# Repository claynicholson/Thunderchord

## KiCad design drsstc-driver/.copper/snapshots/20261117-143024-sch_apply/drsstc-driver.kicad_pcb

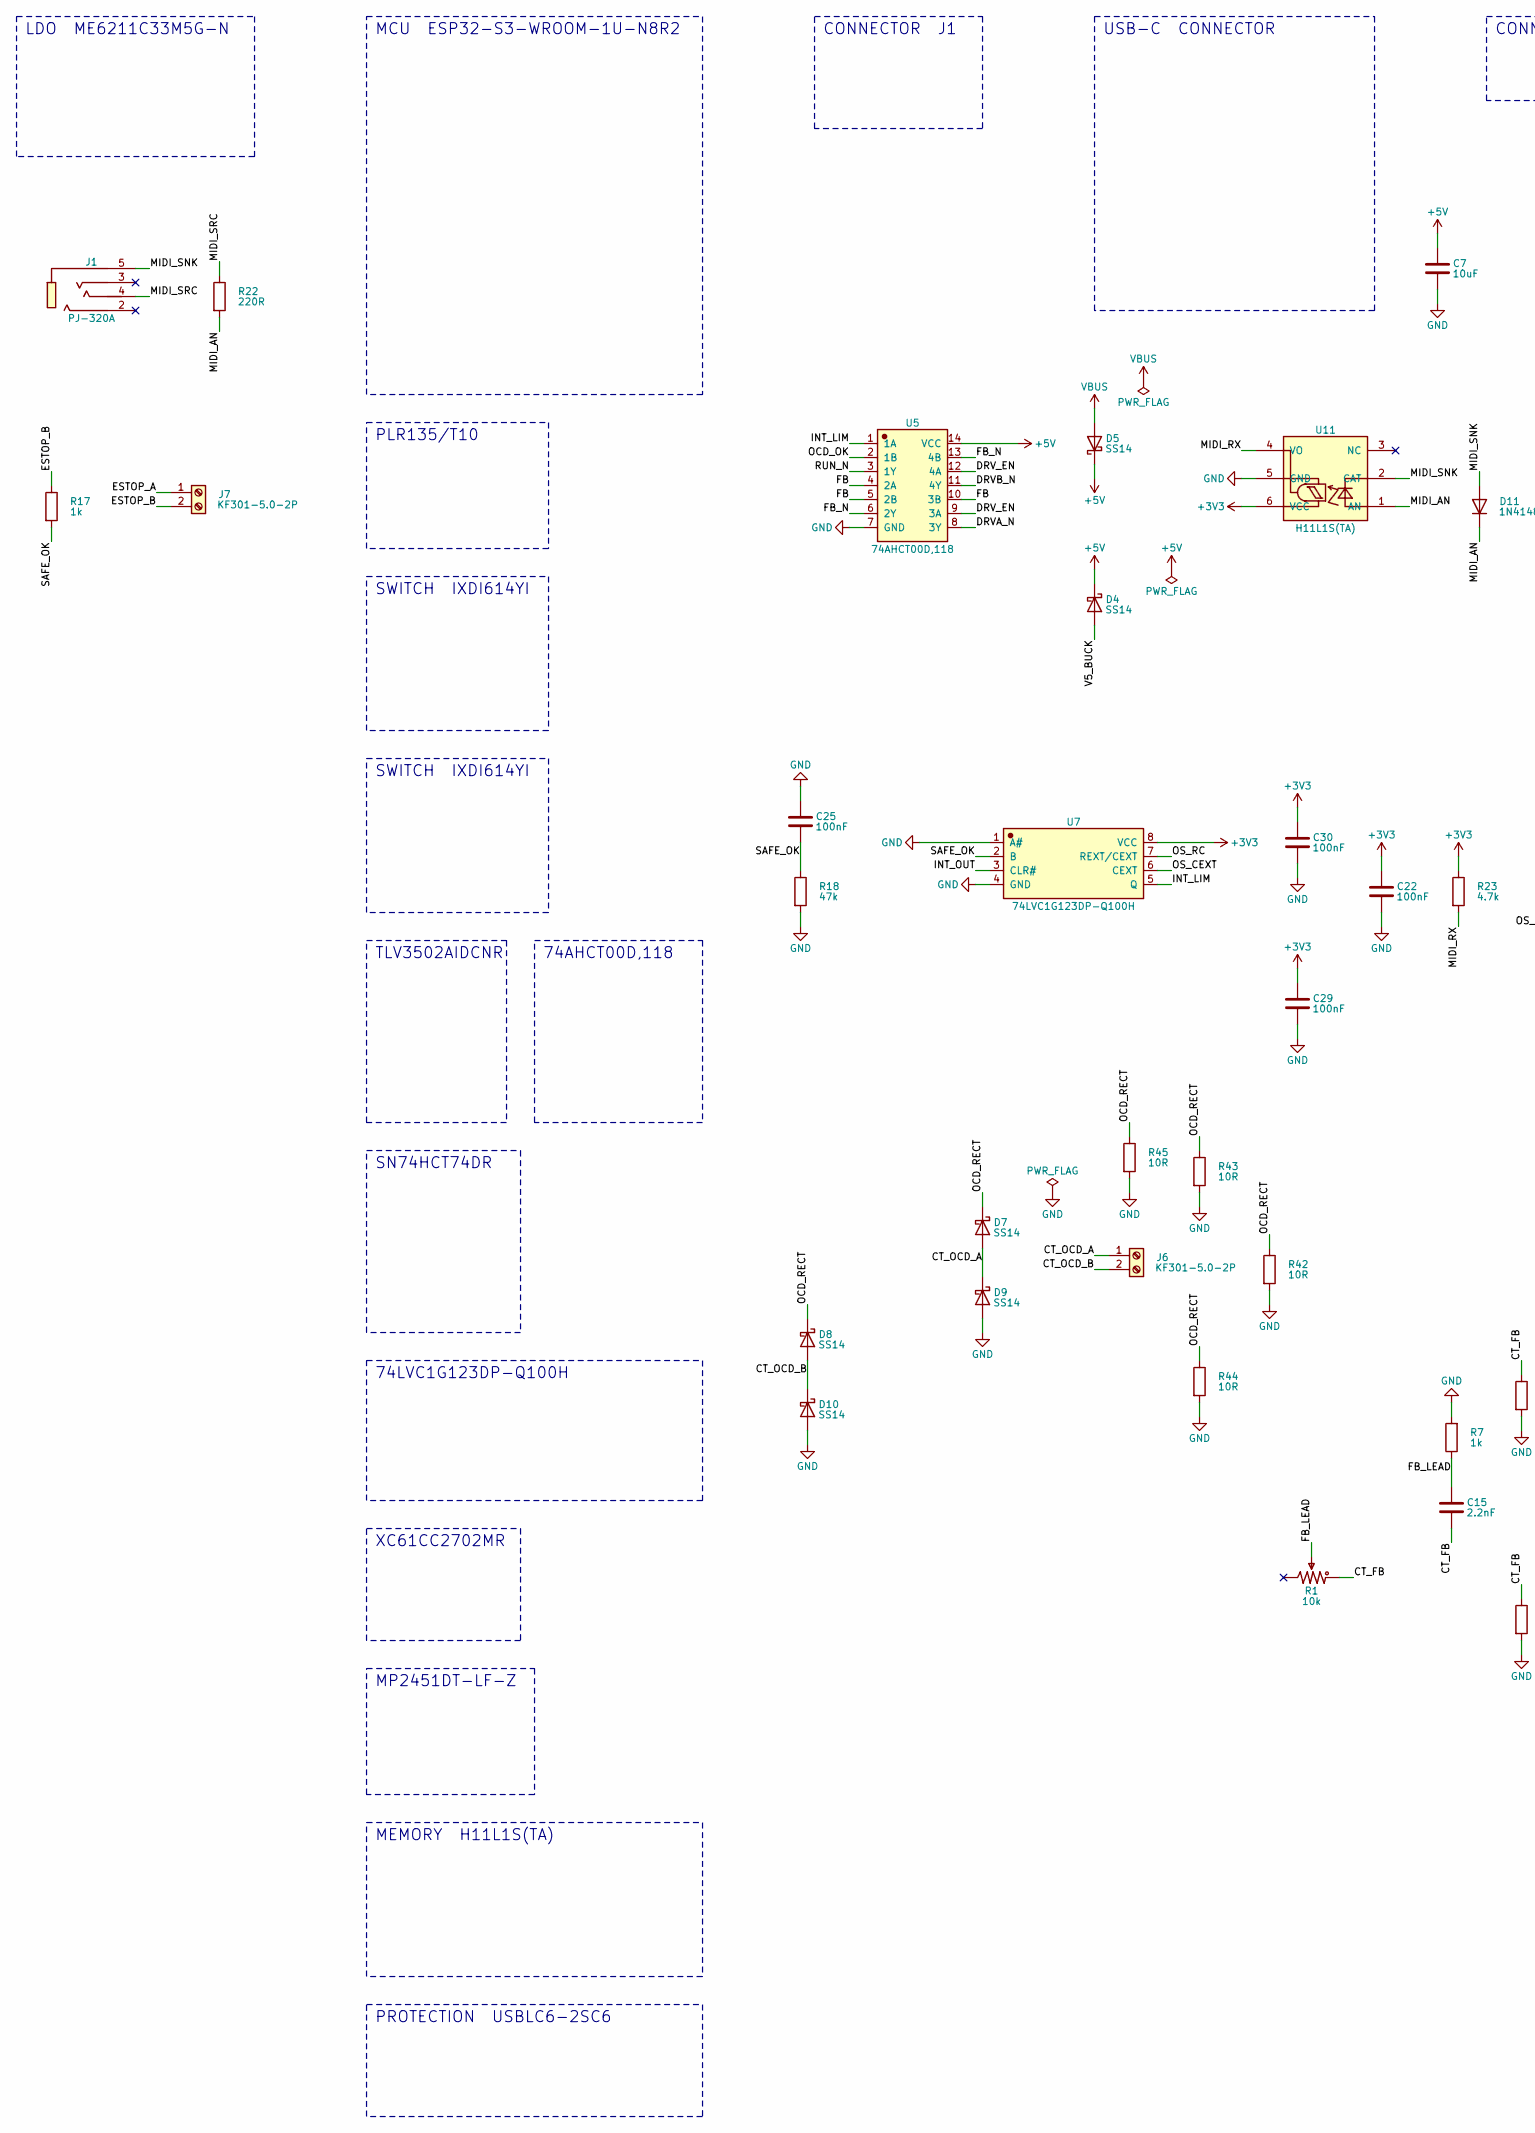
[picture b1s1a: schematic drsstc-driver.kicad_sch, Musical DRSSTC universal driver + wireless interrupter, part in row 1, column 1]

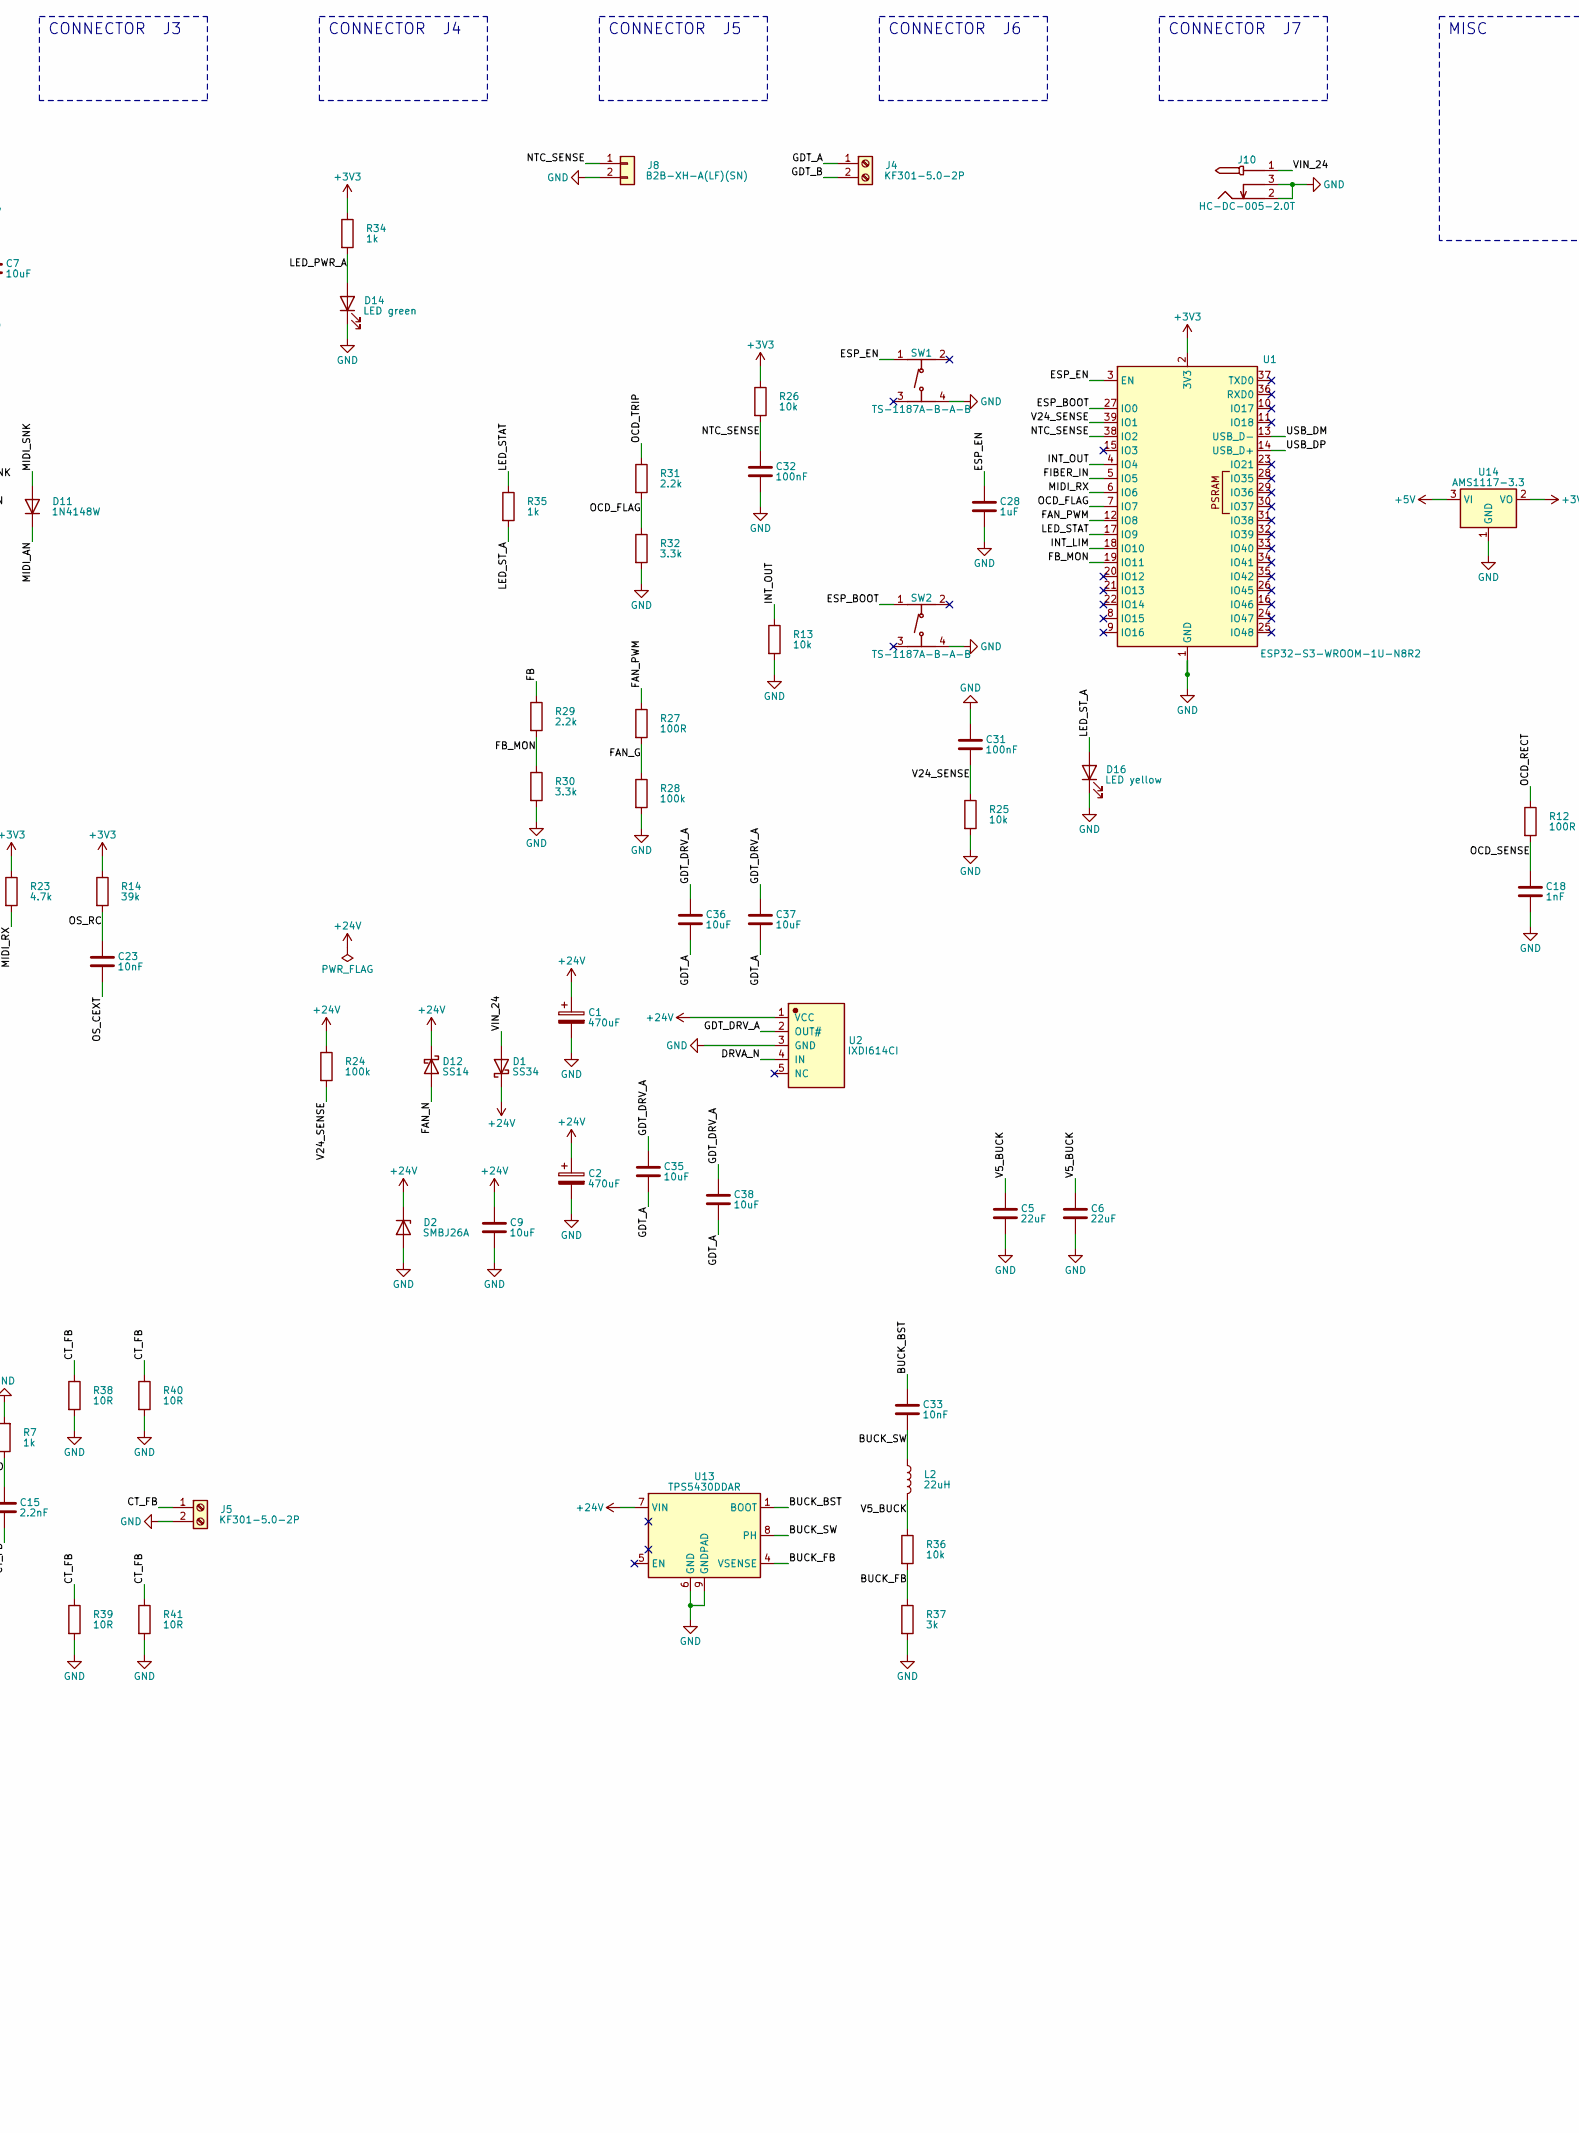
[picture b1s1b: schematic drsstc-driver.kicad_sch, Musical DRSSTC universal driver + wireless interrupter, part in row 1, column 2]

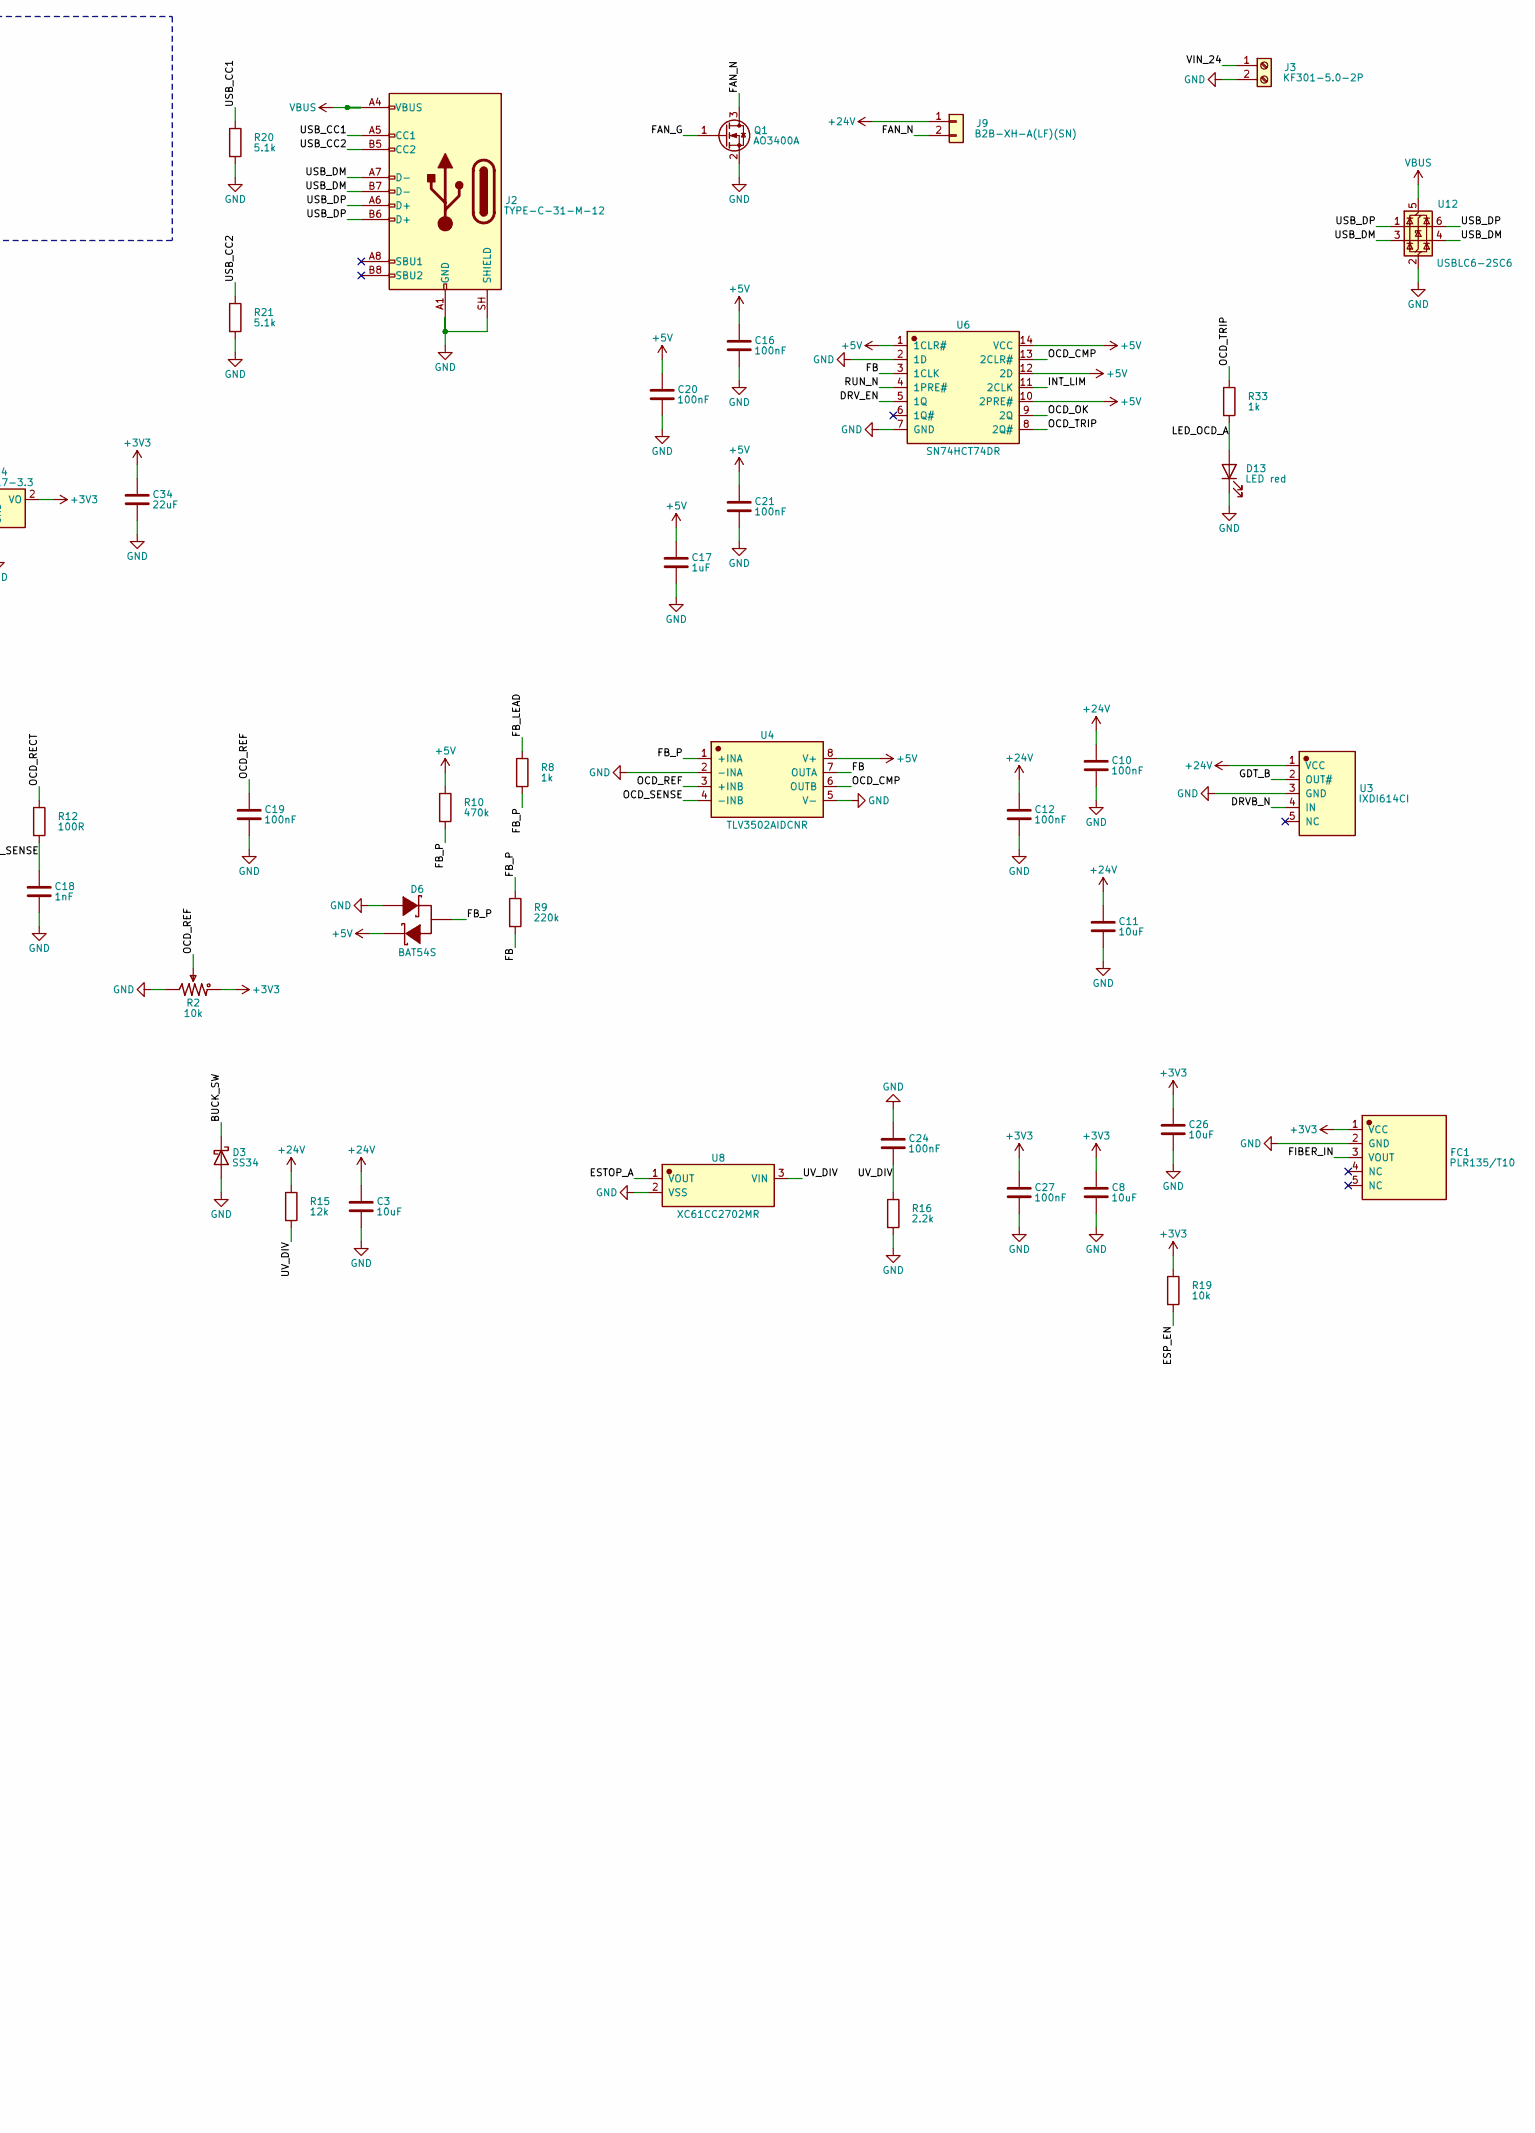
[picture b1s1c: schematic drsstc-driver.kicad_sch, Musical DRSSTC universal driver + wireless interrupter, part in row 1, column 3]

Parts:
C1, C2: 470uF; CP_Elec_8x10.5; MPN RV35V470M8X10; LCSC C48935389
C3, C9, C11, C35, C36, C37, C38: 10uF; C_0805_2012Metric; MPN GRM21BR61H106KE43L; LCSC C440198
C5, C6, C34: 22uF; C_0805_2012Metric; MPN CL21A226MAQNNNE; LCSC C45783
C7, C8, C26: 10uF; C_0805_2012Metric; MPN CL21A106KAYNNNE; LCSC C15850
C10, C12, C16, C19, C20, C21, C22, C24, C25, C27, C29, C30, C31, C32: 100nF; C_0603_1608Metric; MPN CC0603KRX7R9BB104; LCSC C14663
C15: 2.2nF; C_0603_1608Metric; MPN 0603B222K500NT; LCSC C1604
C17, C28: 1uF; C_0603_1608Metric; MPN CL10A105KB8NNNC; LCSC C15849
C18: 1nF; C_0603_1608Metric; MPN CL10B102KB8NNNC; LCSC C1588
C23, C33: 10nF; C_0603_1608Metric; MPN 0603B103K500NT; LCSC C57112
D1, D3: SS34; D_SMA; MPN SS34; LCSC C8678
D2: SMBJ26A; D_SMB; MPN SMBJ26A; LCSC C19077580
D4, D5, D7, D8, D9, D10, D12: SS14; D_SMA; MPN SS14; LCSC C2480
D6: BAT54S; SOT-23-3_L2.9-W1.3-P1.90-LS2.4-BR; MPN BAT54S; LCSC C7420333
D11: 1N4148W; D_SOD-123; MPN 1N4148W; LCSC C81598
D13: LED red; LED_0805_2012Metric; MPN NCD0805R1; LCSC C84256
D14: LED green; LED_0805_2012Metric; MPN KT-0805G; LCSC C2297
D16: LED yellow; LED_0805_2012Metric; MPN KT-0805Y; LCSC C2296
FC1: PLR135/T10; COMM-TH_PLR135-T10; MPN PLR135/T10; LCSC C133279
J1: PJ-320A; AUDIO-TH_XKB_PJ-320A; MPN PJ-320A; LCSC C2884926
J2: TYPE-C-31-M-12; USB_C_Receptacle_HRO_TYPE-C-31-M-12; MPN TYPE-C-31-M-12; LCSC C165948
J3, J4, J5, J6, J7: KF301-5.0-2P; CONN-TH_P5.00_KF301-5.0-2P; MPN KF301-5.0-2P; LCSC C474881
J8, J9: B2B-XH-A(LF)(SN); JST_XH_B2B-XH-A_1x02_P2.50mm_Vertical; MPN B2B-XH-A(LF)(SN); LCSC C158012
J10: HC-DC-005-2.0T; DC-IN-TH_HC-DC-005-2.0T; MPN HC-DC-005-2.0T; LCSC C3010533
L2: 22uH; IND-SMD_L4.0-W4.0_SLW4010S; MPN SWPA4030S220MT; LCSC C83472
Q1: AO3400A; SOT-23; MPN AO3400A; LCSC C20917
R1, R2: 10k; Potentiometer_Bourns_3296W_Vertical; MPN 3296W-1-103; LCSC C118954
R7, R8, R17, R33, R34, R35: 1k; R_0603_1608Metric; MPN 0603WAF1001T5E; LCSC C21190
R9: 220k; R_0603_1608Metric; MPN 0603WAF2203T5E; LCSC C22961
R10: 470k; R_0603_1608Metric; MPN 0603WAF4703T5E; LCSC C23178
R12, R27: 100R; R_0603_1608Metric; MPN 0603WAF1000T5E; LCSC C22775
R13, R19, R25, R26, R36: 10k; R_0603_1608Metric; MPN 0603WAF1002T5E; LCSC C25804
R14: 39k; R_0603_1608Metric; MPN 0603WAF3902T5E; LCSC C23153
R15: 12k; R_0603_1608Metric; MPN 0603WAF1202T5E; LCSC C22790
R16, R29, R31: 2.2k; R_0603_1608Metric; MPN 0603WAF2201T5E; LCSC C4190
R18: 47k; R_0603_1608Metric; MPN 0603WAF4702T5E; LCSC C25819
R20, R21: 5.1k; R_0603_1608Metric; MPN 0603WAF5101T5E; LCSC C23186
R22: 220R; R_0603_1608Metric; MPN 0603WAF2200T5E; LCSC C22962
R23: 4.7k; R_0603_1608Metric; MPN 0603WAF4701T5E; LCSC C23162
R24, R28: 100k; R_0603_1608Metric; MPN 0603WAF1003T5E; LCSC C25803
R30, R32: 3.3k; R_0603_1608Metric; MPN 0603WAF3301T5E; LCSC C22978
R37: 3k; R_0603_1608Metric; MPN 0603WAF3001T5E; LCSC C4211
R38, R39, R40, R41, R42, R43, R44, R45: 10R; R_1206_3216Metric; MPN 1206W4F100JT5E; LCSC C17903
SW1, SW2: TS-1187A-B-A-B; SW-SMD_4P-L5.1-W5.1-P3.70-LS6.5-TL_H1.5; MPN TS-1187A-B-A-B; LCSC C318884
U1: ESP32-S3-WROOM-1U-N8R2; ESP32-S3-WROOM-1U_via0p3; MPN ESP32-S3-WROOM-1U-N8R2; LCSC C3013944
U2, U3: IXDI614CI; TO-220-5L_L10.2-W4.5-P1.70-BL; MPN IXDI614CI; LCSC C1549553
U4: TLV3502AIDCNR; TSOT-23-8_L2.9-W1.6-P0.65-LS2.8-BR; MPN TLV3502AIDCNR; LCSC C48618
U5: 74AHCT00D,118; SOP-14_L8.6-W3.9-P1.27-LS6.0-BL; MPN 74AHCT00D,118; LCSC C554462
U6: SN74HCT74DR; SOIC-14_L8.7-W3.9-P1.27-LS6.0-BL; MPN SN74HCT74DR; LCSC C352961
U7: 74LVC1G123DP-Q100H; TSSOP-8_L3.0-W3.0-P0.65-LS4.0-BL; MPN 74LVC1G123DP-Q100H; LCSC C548244
U8: XC61CC2702MR; SOT-23-3_L2.9-W1.6-P1.90-LS2.8-BR; MPN XC61CC2702MR; LCSC C216611
U11: H11L1S(TA); SMD-6_L7.3-W6.5-P2.54-LS10.2-BL; MPN H11L1S(TA); LCSC C78589
U12: USBLC6-2SC6; SOT-23-6; MPN USBLC6-2SC6; LCSC C7519
U13: TPS5430DDAR; TI_SO-PowerPAD-8_ThermalVias; MPN TPS5430DDAR; LCSC C9864
U14: AMS1117-3.3; SOT-223-3_TabPin2; MPN AMS1117-3.3; LCSC C6186

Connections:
+3V3: C8.1, C22.1, C26.1, C27.1, C29.1, C30.1, C34.1, FC1.1 (VCC), R2.1, R14.1, R19.1, R23.1, R26.1, R34.1, U1.2 (3V3), U7.8 (VCC), U11.6 (VCC), U14.2 (VO)
+5V: C7.1, C16.1, C17.1, C20.1, C21.1, D4.1 (K), D5.1 (K), D6.2 (K2), R10.1, U4.8 (V+), U5.14 (VCC), U6.1 (1CLR#), U6.10 (2PRE#), U6.12 (2D), U6.14 (VCC), U14.3 (VI)
+24V: C1.1, C2.1, C3.1, C9.1, C10.1, C11.1, C12.1, D1.1 (K), D2.1 (K), D12.1 (K), J9.1, R15.1, R24.1, U2.1 (VCC), U3.1 (VCC), U13.7 (VIN)
/BUCK_BST: C33.1, U13.1 (BOOT)
/BUCK_FB: R36.2, R37.1, U13.4 (VSENSE)
/BUCK_SW: C33.2, D3.1 (K), L2.1, U13.8 (PH)
/CT_FB: C15.1, J5.1, R1.1, R38.1, R39.1, R40.1, R41.1
/CT_OCD_A: D7.2 (A), D9.1 (K), J6.1
/CT_OCD_B: D8.2 (A), D10.1 (K), J6.2
/DRVA_N: U2.4 (IN), U5.8 (3Y)
/DRVB_N: U3.4 (IN), U5.11 (4Y)
/DRV_EN: U5.9 (3A), U5.12 (4A), U6.5 (1Q)
/ESP_BOOT: SW2.1 (A), U1.27 (IO0)
/ESP_EN: C28.1, R19.2, SW1.1 (A), U1.3 (EN)
/ESTOP_A: J7.1, U8.1 (VOUT)
/ESTOP_B: J7.2, R17.1
/FAN_G: Q1.1 (G), R27.2, R28.1
/FAN_N: D12.2 (A), J9.2, Q1.3 (D)
/FAN_PWM: R27.1, U1.12 (IO8)
/FB: R9.2, R29.1, U4.7 (OUTA), U5.4 (2A), U5.5 (2B), U5.10 (3B), U6.3 (1CLK)
/FB_LEAD: C15.2, R1.2, R7.1, R8.1
/FB_MON: R29.2, R30.1, U1.19 (IO11)
/FB_N: U5.6 (2Y), U5.13 (4B)
/FB_P: D6.3 (A), R8.2, R9.1, R10.2, U4.1 (+INA)
/FIBER_IN: FC1.3 (VOUT), U1.5 (IO5)
/GDT_A: C35.2, C36.2, C37.2, C38.2, J4.1
/GDT_B: J4.2, U3.2 (OUT#)
/GDT_DRV_A: C35.1, C36.1, C37.1, C38.1, U2.2 (OUT#)
/INT_LIM: U1.18 (IO10), U5.1 (1A), U6.11 (2CLK), U7.5 (Q)
/INT_OUT: R13.1, U1.4 (IO4), U7.3 (CLR#)
/LED_OCD_A: D13.2 (A), R33.2
/LED_PWR_A: D14.2 (A), R34.2
/LED_STAT: R35.1, U1.17 (IO9)
/LED_ST_A: D16.2 (A), R35.2
/MIDI_AN: D11.1 (K), R22.2, U11.1 (AN)
/MIDI_RX: R23.2, U1.6 (IO6), U11.4 (VO)
/MIDI_SNK: D11.2 (A), J1.5, U11.2 (CAT)
/MIDI_SRC: J1.4, R22.1
/NTC_SENSE: C32.1, J8.1, R26.2, U1.38 (IO2)
/OCD_CMP: U4.6 (OUTB), U6.13 (2CLR#)
/OCD_FLAG: R31.2, R32.1, U1.7 (IO7)
/OCD_OK: U5.2 (1B), U6.9 (2Q)
/OCD_RECT: D7.1 (K), D8.1 (K), R12.1, R42.1, R43.1, R44.1, R45.1
/OCD_REF: C19.1, R2.2, U4.3 (+INB)
/OCD_SENSE: C18.1, R12.2, U4.4 (-INB)
/OCD_TRIP: R31.1, R33.1, U6.8 (2Q#)
/OS_CEXT: C23.1, U7.6 (CEXT)
/OS_RC: C23.2, R14.2, U7.7 (REXT/CEXT)
/RUN_N: U5.3 (1Y), U6.4 (1PRE#)
/SAFE_OK: C25.1, R17.2, R18.1, U7.2 (B)
/USB_CC1: J2.A5 (CC1), R20.1
/USB_CC2: J2.B5 (CC2), R21.1
/USB_DM: J2.A7 (D-), J2.B7 (D-), U1.13 (USB_D-), U12.3 (I/O2), U12.4 (I/O2)
/USB_DP: J2.A6 (D+), J2.B6 (D+), U1.14 (USB_D+), U12.1 (I/O1), U12.6 (I/O1)
/UV_DIV: C24.1, R15.2, R16.1, U8.3 (VIN)
/V5_BUCK: C5.1, C6.1, D4.2 (A), L2.2, R36.1
/V24_SENSE: C31.1, R24.2, R25.1, U1.39 (IO1)
/VIN_24: D1.2 (A), J3.1, J10.1
GND: C1.2, C2.2, C3.2, C5.2, C6.2, C7.2, C8.2, C9.2, C10.2, C11.2, C12.2, C16.2, C17.2, C18.2, C19.2, C20.2, C21.2, C22.2, C24.2, C25.2, C26.2, C27.2, C28.2, C29.2, C30.2, C31.2, C32.2, C34.2, D2.2 (A), D3.2 (A), D6.1 (K1), D9.2 (A), D10.2 (A), D13.1 (K), D14.1 (K), D16.1 (K), FC1.2 (GND), J2.A1 (GND), J2.A12 (GND), J2.B1 (GND), J2.B12 (GND), J2.SH (SHIELD), J3.2, J5.2, J8.2, J10.2, J10.3, Q1.2 (S), R2.3, R7.2, R13.2, R16.2, R18.2, R20.2, R21.2, R25.2, R28.2, R30.2, R32.2, R37.2, R38.2, R39.2, R40.2, R41.2, R42.2, R43.2, R44.2, R45.2, SW1.4 (D), SW2.4 (D), U1.1 (GND), U1.40 (GND), U1.41 (GND), U2.3 (GND), U3.3 (GND), U4.2 (-INA), U4.5 (V-), U5.7 (GND), U6.2 (1D), U6.7 (GND), U7.1 (A#), U7.4 (GND), U8.2 (VSS), U11.5 (GND), U12.2 (GND), U13.6 (GND), U13.9 (GNDPAD), U14.1 (GND)
VBUS: D5.2 (A), J2.A4 (VBUS), J2.A9 (VBUS), J2.B4 (VBUS), J2.B9 (VBUS), U12.5 (VBUS)

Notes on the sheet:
CONNECTOR J6
CONNECTOR J3
CONNECTOR J5
TLV3502AIDCNR
XC61CC2702MR
LDO ME6211C33M5G-N
MP2451DT-LF-Z
SN74HCT74DR
CONNECTOR J4
MISC
PROTECTION USBLC6-2SC6
SWITCH IXDI614YI
MEMORY H11L1S(TA)
CONNECTOR J7
74LVC1G123DP-Q100H
CONNECTOR J1
USB-C CONNECTOR
74AHCT00D,118
MCU ESP32-S3-WROOM-1U-N8R2
PLR135/T10

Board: 4 copper layers, 121 parts (0 on the bottom side), 60 nets, no tracks yet.

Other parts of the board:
H1, H2, H3, H4: M3; MountingHole_3.2mm_M3
